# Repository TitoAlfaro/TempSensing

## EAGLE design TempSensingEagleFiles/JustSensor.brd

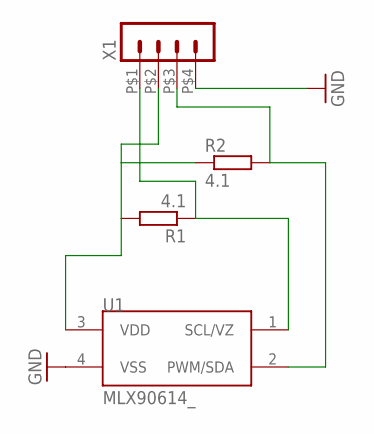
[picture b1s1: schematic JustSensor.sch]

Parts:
R1, R2: 4.1; 0204/7
U1: MLX90614_; TO-39
X1: HEADER_POS4_43045-0401; 43045-0400

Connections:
GND: U1.4 (VSS), X1.P$4 (4)
unnamed: R1.2, R2.1, U1.3 (VDD), X1.P$2 (2)
unnamed: R1.1, U1.1 (SCL/VZ), X1.P$1 (1)
unnamed: R2.2, U1.2 (PWM/SDA), X1.P$3 (3)

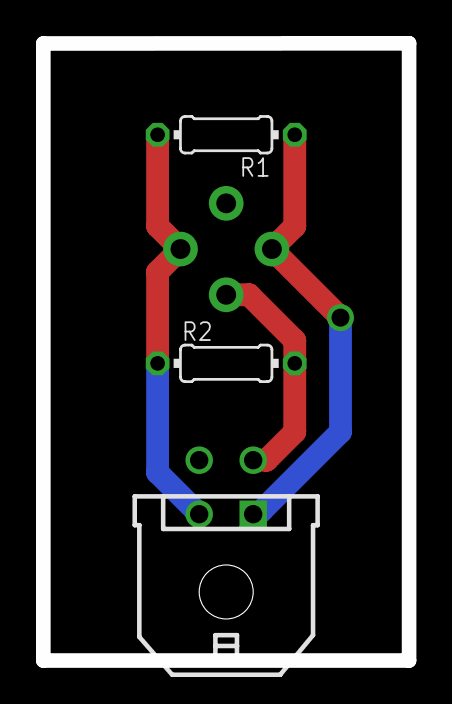
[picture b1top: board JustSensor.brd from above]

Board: 2 copper layers, 20.3 x 34.3 mm, 4 parts (1 on the bottom side), 4 nets.

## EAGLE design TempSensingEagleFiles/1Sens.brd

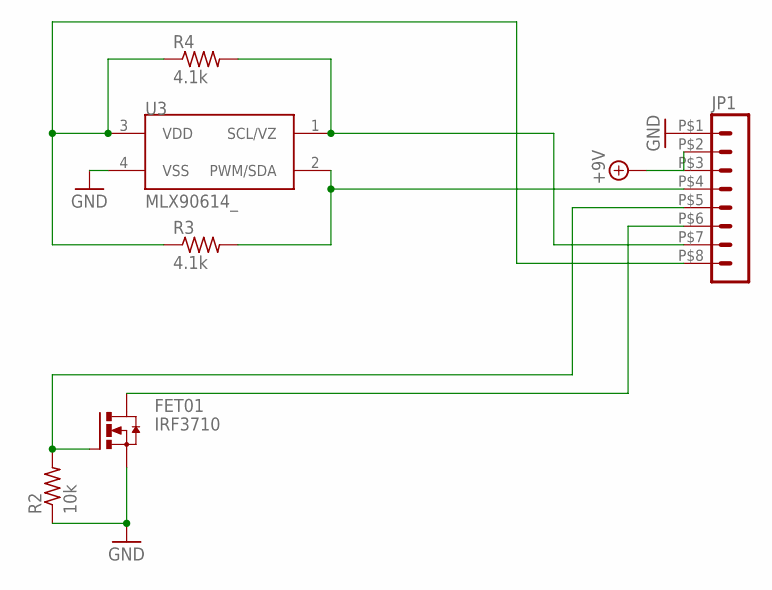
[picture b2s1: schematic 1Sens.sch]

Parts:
FET01: IRF3710; TO220AH
JP1: HEADER_POS8_43045-0800; 43045-0800
R2: 10k; 0207/7
R3, R4: 4.1k; 0204/5
U3: MLX90614_; TO-39

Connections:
+9V: JP1.P$2 (2), JP1.P$3 (3)
GND: FET01.E (S), JP1.P$1 (1), R2.1, U3.4 (VSS)
unnamed: JP1.P$8 (8), R3.1, R4.1, U3.3 (VDD)
unnamed: FET01.C (D), JP1.P$6 (6)
unnamed: JP1.P$7 (7), R4.2, U3.1 (SCL/VZ)
unnamed: JP1.P$4 (4), R3.2, U3.2 (PWM/SDA)
unnamed: FET01.B (G), JP1.P$5 (5), R2.2

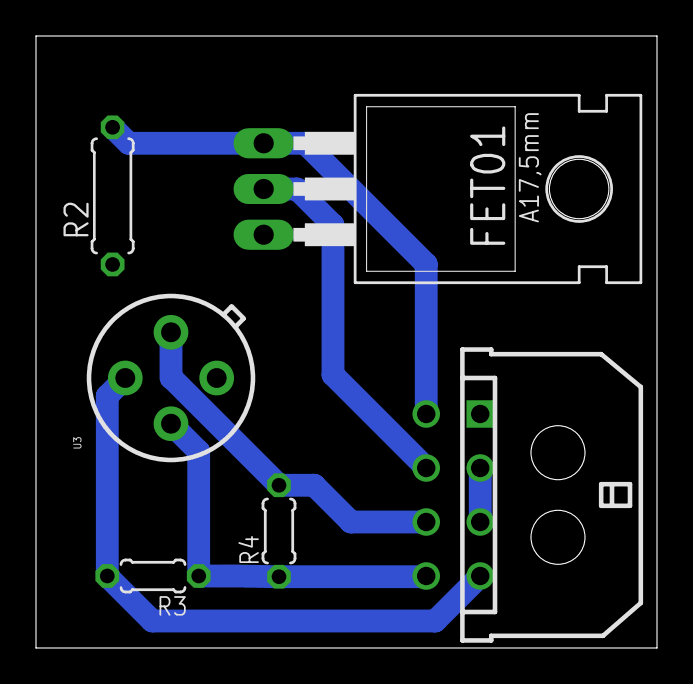
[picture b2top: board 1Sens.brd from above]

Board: 2 copper layers, 34.5 x 34.0 mm, 6 parts (0 on the bottom side), 7 nets.

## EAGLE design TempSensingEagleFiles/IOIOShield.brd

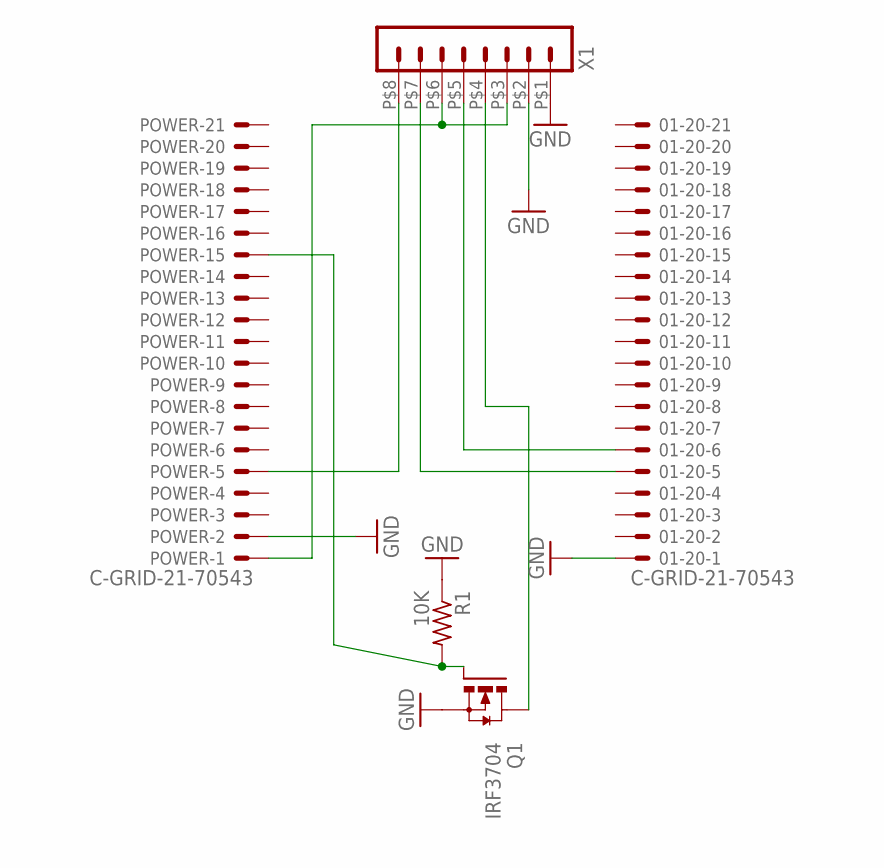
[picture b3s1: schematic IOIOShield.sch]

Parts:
01-20: C-GRID-21-70543; 70543-21
POWER: C-GRID-21-70543; 70543-21
Q1: IRF3704; TO220AH
R1: 10K; 0204/7
X1: HEADER_POS8_43045-0800; 43045-0800

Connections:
GND: 01-20.1, POWER.2, Q1.E (S), R1.1, X1.P$1 (1), X1.P$2 (2)
unnamed: POWER.15, Q1.B (G), R1.2
unnamed: Q1.C (D), X1.P$4 (4)
unnamed: POWER.1, X1.P$3 (3), X1.P$6 (6)
unnamed: POWER.5, X1.P$8 (8)
unnamed: 01-20.6, X1.P$5 (5)
unnamed: 01-20.5, X1.P$7 (7)

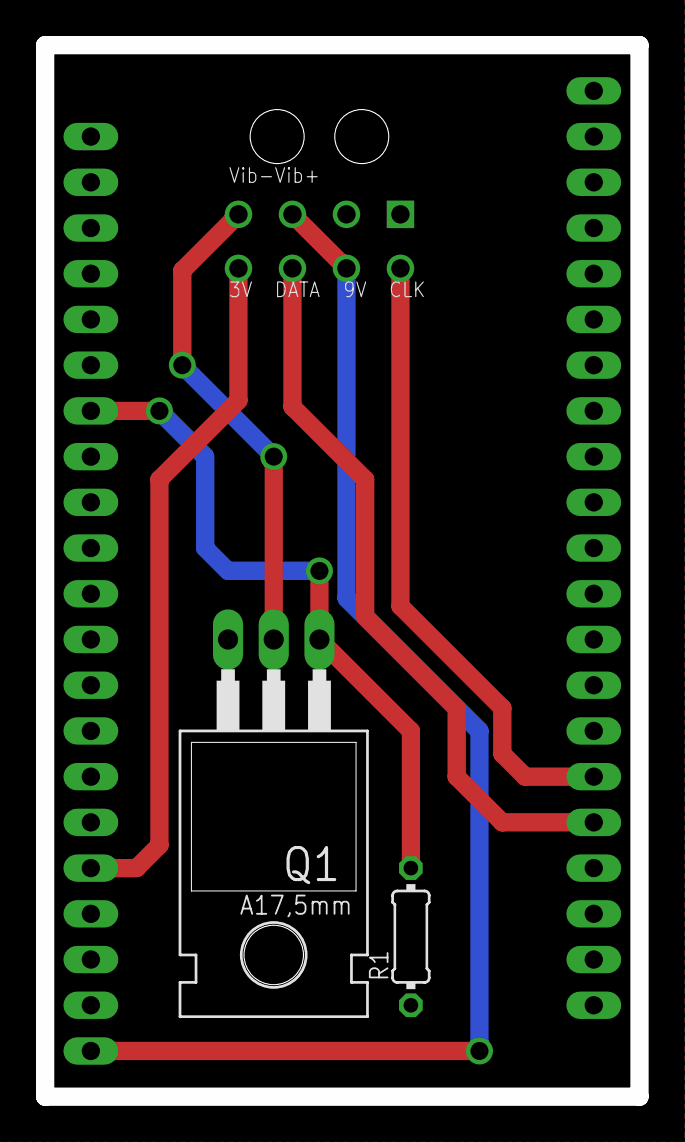
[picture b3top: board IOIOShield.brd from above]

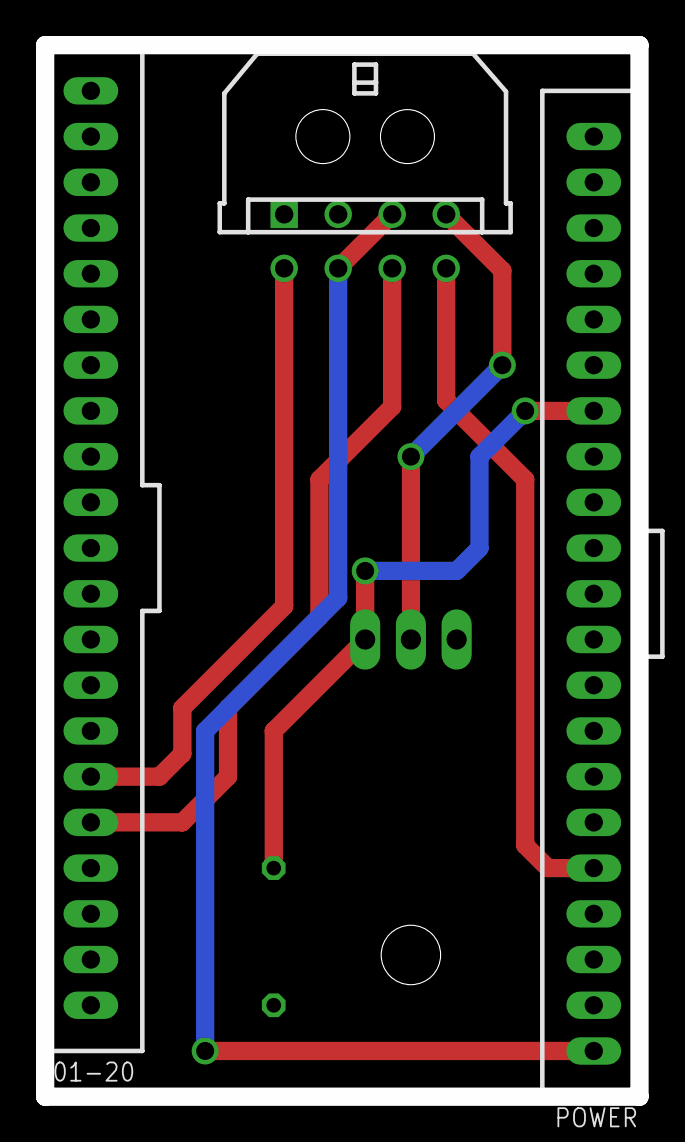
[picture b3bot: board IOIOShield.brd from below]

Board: 2 copper layers, 33.0 x 58.4 mm, 5 parts (3 on the bottom side), 7 nets.

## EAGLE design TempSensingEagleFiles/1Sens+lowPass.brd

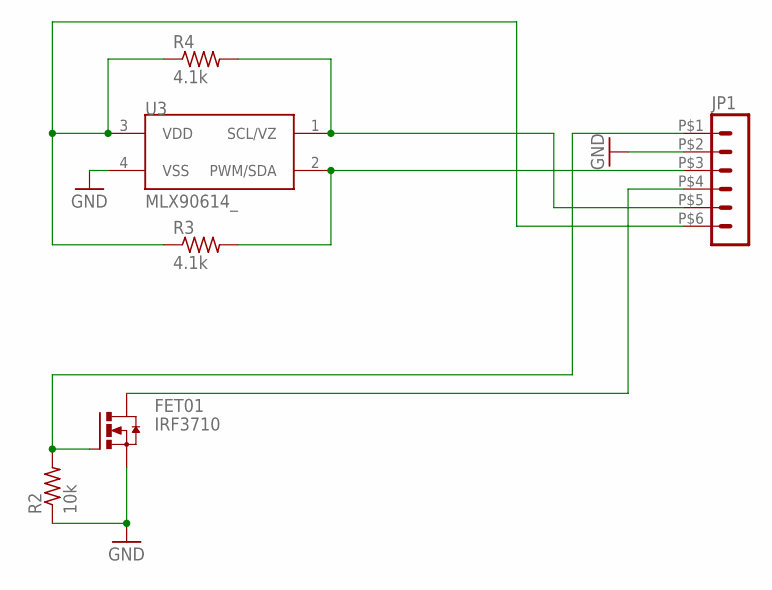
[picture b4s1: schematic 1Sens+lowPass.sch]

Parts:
FET01: IRF3710; TO220AH
JP1: HEADER_POS6_43045-0600; 43045-0600
R2: 10k; 0207/7
R3, R4: 4.1k; 0204/5
U3: MLX90614_; TO-39

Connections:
GND: FET01.E (S), JP1.P$2 (2), R2.1, U3.4 (VSS)
unnamed: JP1.P$6 (6), R3.1, R4.1, U3.3 (VDD)
unnamed: FET01.C (D), JP1.P$4 (4)
unnamed: JP1.P$5 (5), R4.2, U3.1 (SCL/VZ)
unnamed: JP1.P$3 (3), R3.2, U3.2 (PWM/SDA)
unnamed: FET01.B (G), JP1.P$1 (1), R2.2

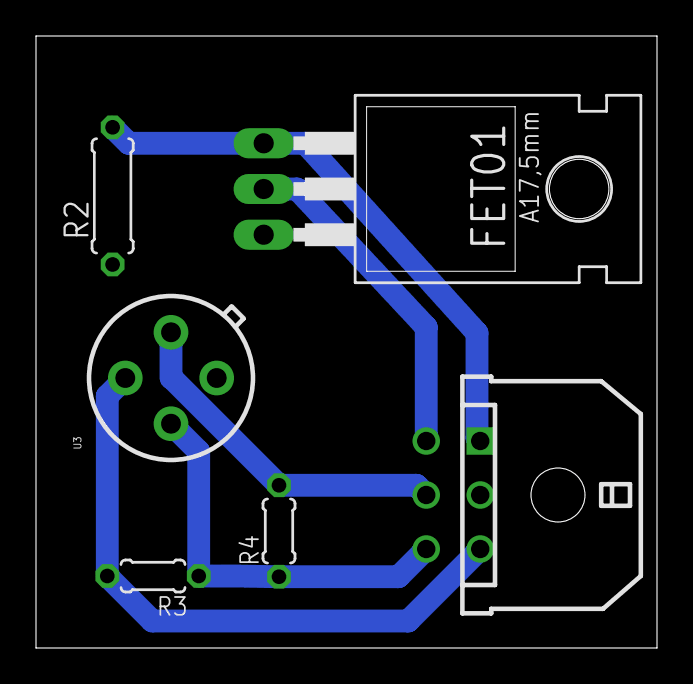
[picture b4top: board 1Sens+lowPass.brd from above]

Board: 2 copper layers, 34.5 x 34.0 mm, 6 parts (0 on the bottom side), 6 nets.

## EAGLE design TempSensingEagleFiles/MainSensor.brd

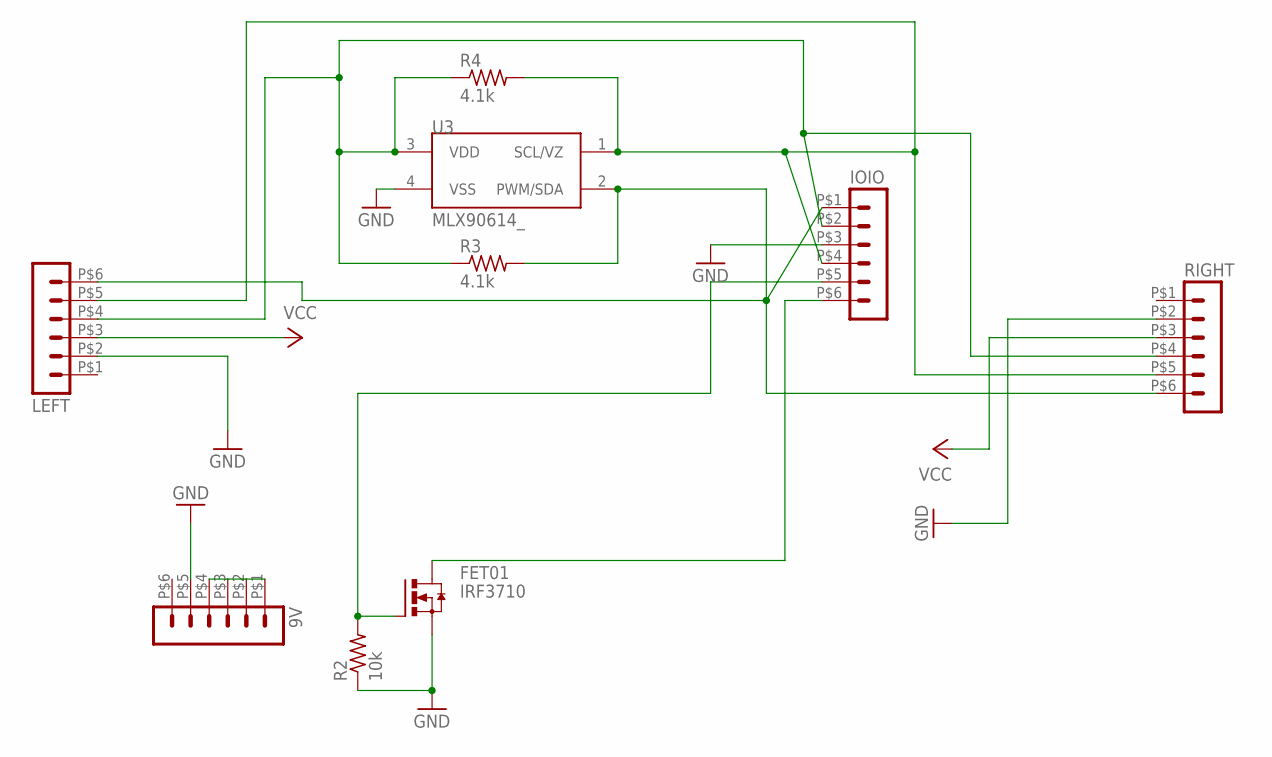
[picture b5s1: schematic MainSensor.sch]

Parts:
9V: HEADER_POS6_43045-0600; 43045-0600
FET01: IRF3710; TO220AH
IOIO: HEADER_POS6_43045-0600; 43045-0600
LEFT: HEADER_POS6_43045-0600; 43045-0600
R2: 10k; 0207/7
R3, R4: 4.1k; 0204/5
RIGHT: HEADER_POS6_43045-0600; 43045-0600
U3: MLX90614_; TO-39

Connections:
3.3V: IOIO.P$2 (2), LEFT.P$4 (4), R3.1, R4.1, RIGHT.P$4 (4), U3.3 (VDD)
GND: 9V.P$5 (5), FET01.E (S), IOIO.P$3 (3), LEFT.P$2 (2), R2.1, RIGHT.P$2 (2), U3.4 (VSS)
IOIOPIN: FET01.B (G), IOIO.P$5 (5), R2.2
unnamed: 9V.P$1 (1), 9V.P$2 (2), 9V.P$3 (3), 9V.P$4 (4)
SCL: IOIO.P$4 (4), LEFT.P$5 (5), R4.2, RIGHT.P$5 (5), U3.1 (SCL/VZ)
SDA: IOIO.P$1 (1), LEFT.P$6 (6), R3.2, RIGHT.P$6 (6), U3.2 (PWM/SDA)
VCC: LEFT.P$3 (3), RIGHT.P$3 (3)
VIB: FET01.C (D), IOIO.P$6 (6)

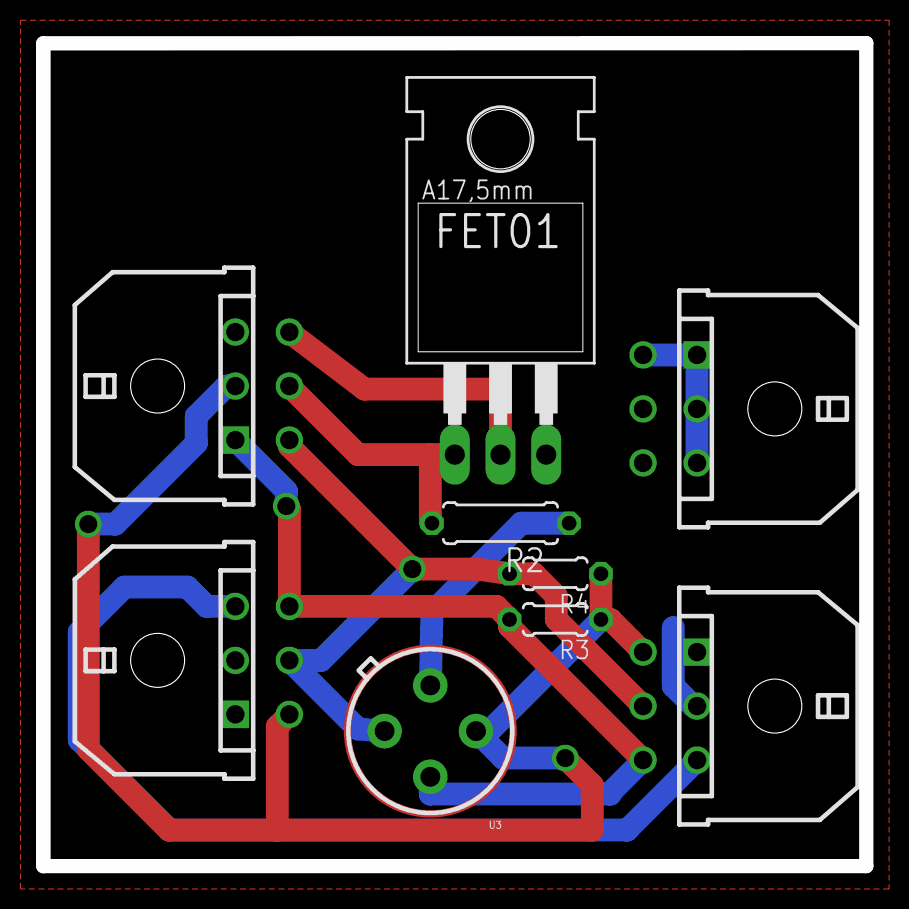
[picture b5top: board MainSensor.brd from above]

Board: 2 copper layers, 45.7 x 45.7 mm, 9 parts (0 on the bottom side), 8 nets.

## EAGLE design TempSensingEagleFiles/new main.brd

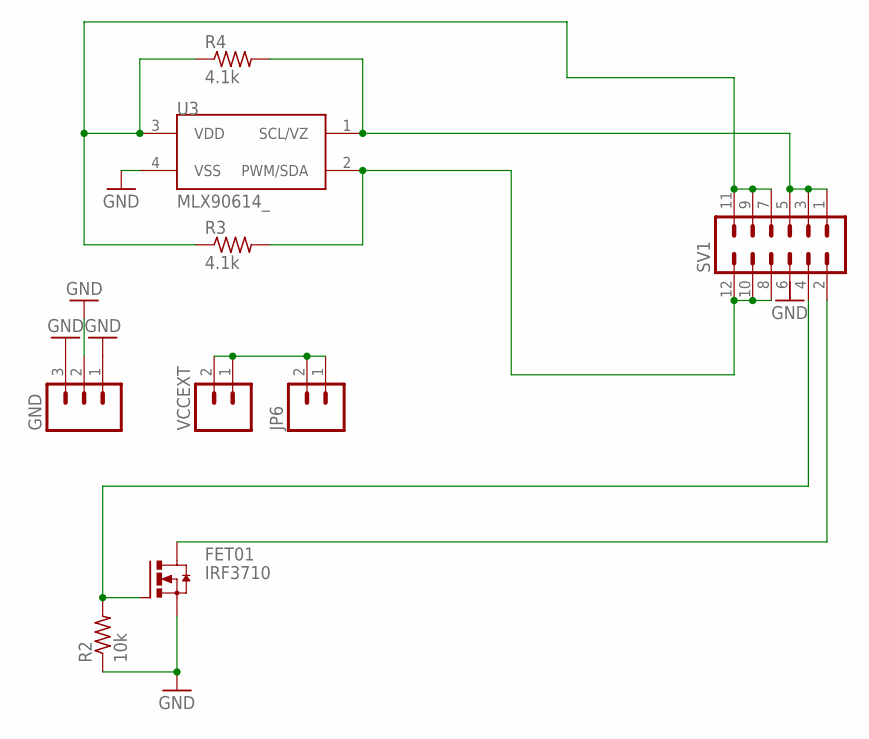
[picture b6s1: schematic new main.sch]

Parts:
FET01: IRF3710; TO220AH
GND: M03LONGPADS; 1X03_LONGPADS
JP6: M02LOCK_LONGPADS; 1X02_LOCK_LONGPADS
R2: 10k; 0207/7
R3, R4: 4.1k; 0204/5
SV1: MA06-2
U3: MLX90614_; TO-39
VCCEXT: M02LOCK_LONGPADS; 1X02_LOCK_LONGPADS

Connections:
GND: FET01.E (S), GND.1, GND.2, GND.3, R2.1, U3.4 (VSS)
unnamed: JP6.1, JP6.2, VCCEXT.1, VCCEXT.2
unnamed: FET01.C (D), SV1.2
unnamed: R4.2, SV1.1, SV1.3, SV1.5, U3.1 (SCL/VZ)
unnamed: R3.2, SV1.8, SV1.10, SV1.12, U3.2 (PWM/SDA)
unnamed: FET01.B (G), R2.2, SV1.4
VCC3: R3.1, R4.1, SV1.7, SV1.9, SV1.11, U3.3 (VDD)

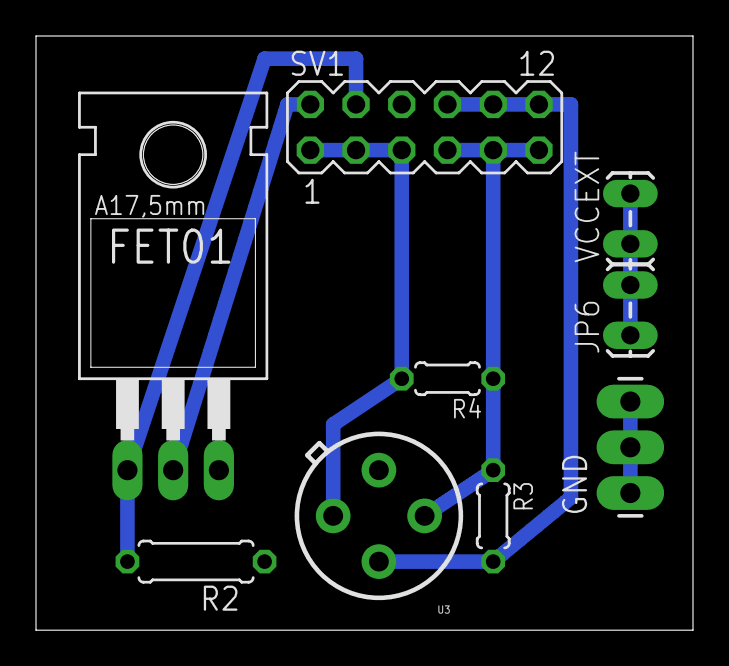
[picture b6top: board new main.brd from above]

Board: 2 copper layers, 36.5 x 33.0 mm, 9 parts (0 on the bottom side), 7 nets.

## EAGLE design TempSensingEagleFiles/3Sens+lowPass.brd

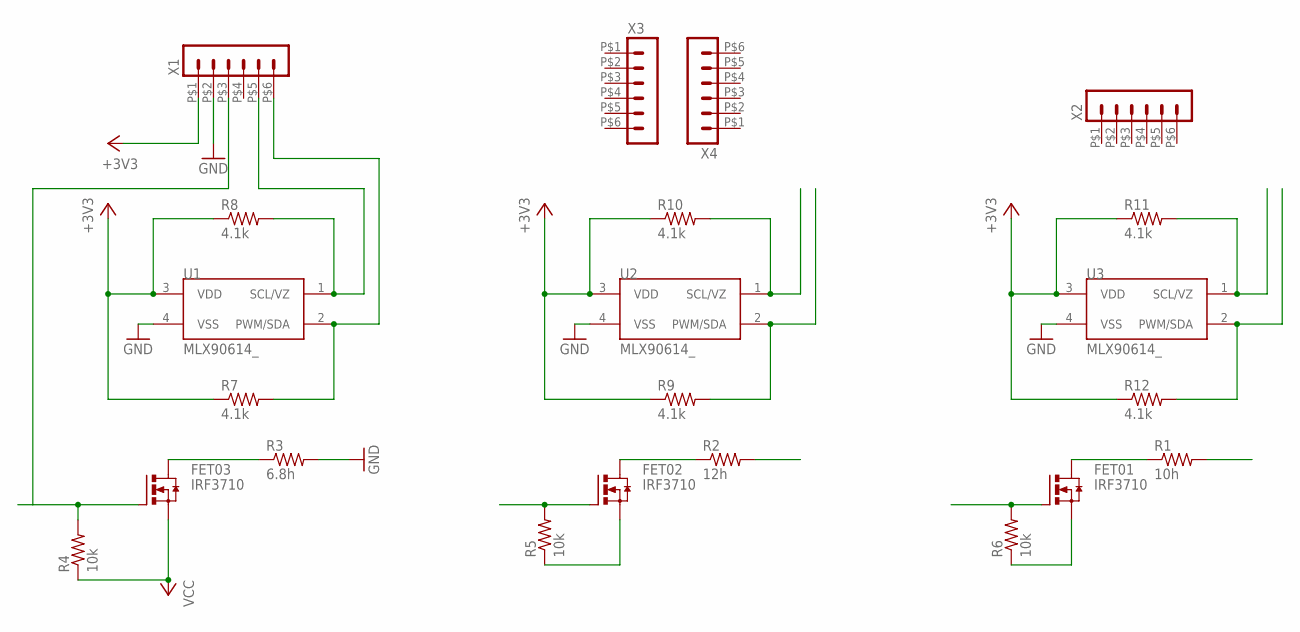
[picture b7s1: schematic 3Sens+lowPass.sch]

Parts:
FET01, FET02, FET03: IRF3710; TO220AH
R1: 10h; 0204V
R2: 12h; 0204V
R3: 6.8h; 0204V
R4, R5, R6: 10k; 0204V
R7, R8, R9, R10, R11, R12: 4.1k; 0204V
U1, U2, U3: MLX90614_; TO-39
X1, X2: HEADER_POS6_43045-0600; 43045-0600
X3, X4: HEADER_POS6_43650-0600; 43650-0600

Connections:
+3V3: R7.1, R8.1, R9.1, R10.1, R11.1, R12.1, U1.3 (VDD), U2.3 (VDD), U3.3 (VDD), X1.P$1 (1)
GND: R3.2, U1.4 (VSS), U2.4 (VSS), U3.4 (VSS), X1.P$2 (2)
unnamed: R8.2, U1.1 (SCL/VZ), X1.P$5 (5)
unnamed: FET02.B (G), R5.2
unnamed: FET02.E (S), R5.1
unnamed: FET01.B (G), R6.2
unnamed: FET01.E (S), R6.1
unnamed: R7.2, U1.2 (PWM/SDA), X1.P$6 (6)
unnamed: FET03.B (G), R4.2, X1.P$3 (3)
unnamed: R10.2, U2.1 (SCL/VZ)
unnamed: R9.2, U2.2 (PWM/SDA)
unnamed: FET03.C (D), R3.1
unnamed: R11.2, U3.1 (SCL/VZ)
unnamed: R12.2, U3.2 (PWM/SDA)
unnamed: FET02.C (D), R2.1
unnamed: FET01.C (D), R1.1
VCC: FET03.E (S), R4.1

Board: 2 copper layers, 22 parts (0 on the bottom side), 17 nets, no tracks yet.

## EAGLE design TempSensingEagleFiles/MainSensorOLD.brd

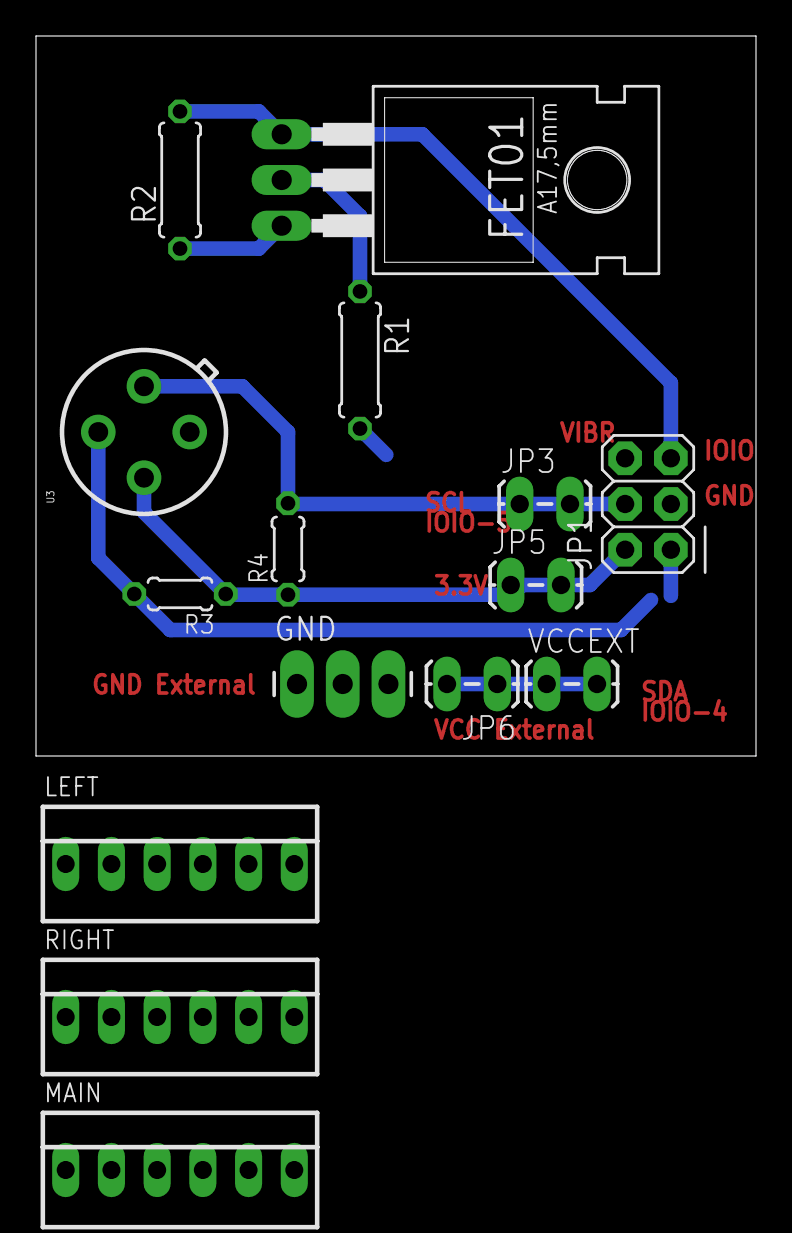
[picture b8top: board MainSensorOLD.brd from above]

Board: 2 copper layers, 40.0 x 40.0 mm, 15 parts (0 on the bottom side), 8 nets.

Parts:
FET01: IRF3710; TO220AH
GND: 1X03_LONGPADS
JP1: 2X03
JP3, JP5, JP6: 1X02_LOCK_LONGPADS
LEFT: 22-23-2061
MAIN: 22-23-2061
R1: 10h; 0207/7
R2: 10k; 0207/7
R3, R4: 4.1k; 0204/5
RIGHT: 22-23-2061
U3: MLX90614_; TO-39
VCCEXT: 1X02_LOCK_LONGPADS

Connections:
GND: FET01.E, GND.1, GND.2, GND.3, JP1.3, R2.1, U3.4
unnamed: JP6.1, JP6.2, VCCEXT.1, VCCEXT.2
unnamed: FET01.C, R1.1
unnamed: JP1.6, R1.2
unnamed: JP1.4, JP3.1, JP3.2, R4.2, U3.1
unnamed: JP1.1, LEFT.6, R3.2, RIGHT.1, U3.2
unnamed: FET01.B, JP1.5, R2.2
VCC3: JP1.2, JP5.1, JP5.2, R3.1, R4.1, U3.3

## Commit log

2014-02-10 after the mess up
2014-02-10 first commit AM
2014-02-11 Changed some of the xml stuff.
2014-03-04 UI Changes
    Now with portrait and landscape! (for small screens, maybe eventually
    one day I’ll add the tablet-sized option)
2014-03-04 also these things changed
2014-03-04 STABLE
    Small changes
2014-03-04 Catching up
2014-03-14 ADDED: Usb to the Manifest
2014-03-19 thread-based vibration
    one thread version.
2014-04-22 added eagle files (+ deletes)
    (there were a bunch of deletes)
2014-05-09 various updates, including eagleFiles
2014-06-12 before merge with Diana
2014-06-12 Changed name of Eagle forlder
2014-06-16 worked on Eagle Files
    Added 1 Sensor and Main board
2014-06-27 STABLE: Added better threading
2014-06-27 Revert "STABLE: Added better threading"
    This reverts commit b74bb6b943322a5487aef219e170d9d2f1191ec7.
2014-06-29 catching up with thread loop
2014-06-29 UNSTABLE: there is a problem with more than 1 thread
2014-07-28 STABLE: working with only one sensor
2014-08-11 ADDED: Lined graph
2014-08-13 HALF STABLE:
    Added logging but BlueTooth is spotty and only works with tablet not
    phone.
2014-08-18 STABLE: with logging and stamping.
2014-08-18 STABLE: Added Turn toggle button.
2014-08-25 STABLE: fixed wording in log
2014-10-07 Changes for new study

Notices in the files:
parts and their libraries:
SparkFun-Sensors: Licensing: CC v3.0 Share-Alike You are welcome to use this library for commercial purposes.
SparkFun-Sensors: Licensing: Creative Commons ShareAlike 4.0 International - https://creativecommons.org/licenses/by-sa/4.0
